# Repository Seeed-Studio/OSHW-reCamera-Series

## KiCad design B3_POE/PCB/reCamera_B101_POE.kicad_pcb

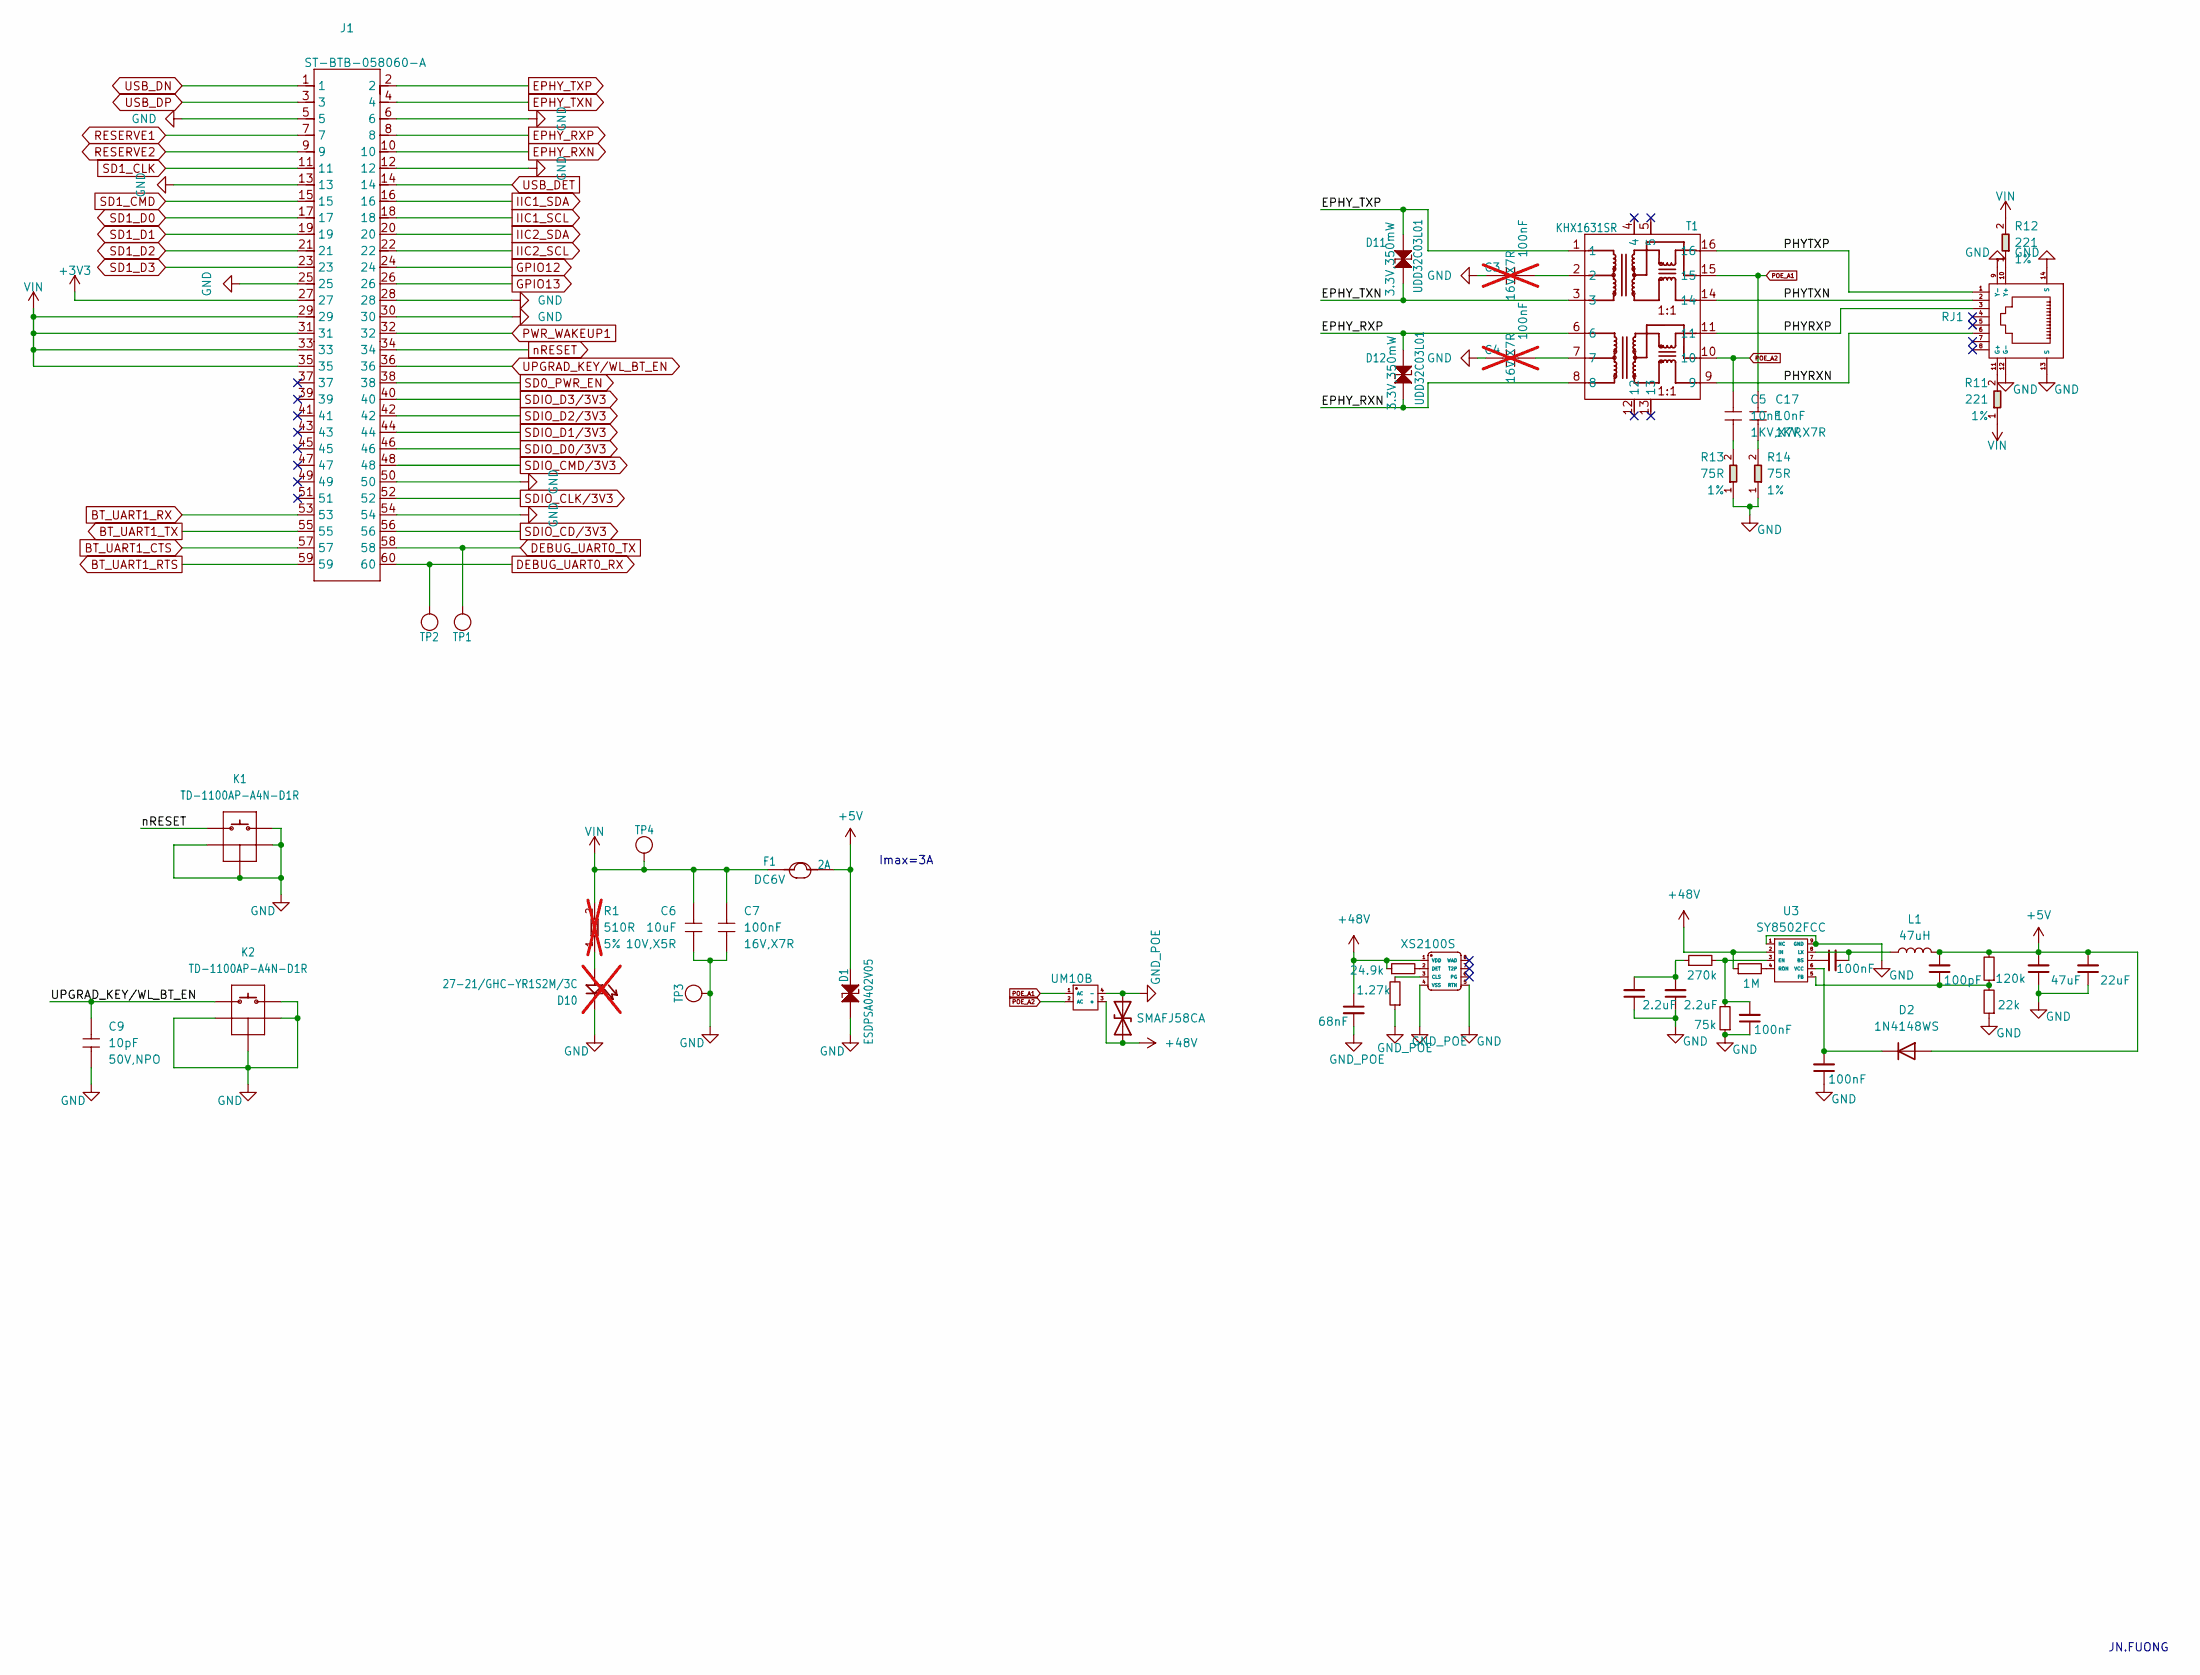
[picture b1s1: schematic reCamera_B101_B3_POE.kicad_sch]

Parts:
C1: 68nF; C_0402_1005Metric
C2, C10: 2.2uF; C_0402_1005Metric
C3, C4: 100nF; C0402; Voltage Rating 16V,X7R; MPN CC0402KRX7R7BB104; not fitted
C5, C17: 10nF; C0402; Voltage Rating 1KV,X7R; MPN CC1206KKX7RCBB102
C6: 10uF; C0402; Voltage Rating 10V,X5R; MPN CC0603KRX5R6BB106
C7: 100nF; C0402; Voltage Rating 16V,X7R; MPN CC0402KRX7R7BB104
C9: 10pF; C0402; Voltage Rating 50V,NPO; MPN CC0402JRNPO9BN100
C11, C12, C13: 100nF; C_0402_1005Metric
C14: 100pF; C_0402_1005Metric
C15: 47uF; C_0402_1005Metric
C16: 22uF; C_0402_1005Metric
D1: ESDPSA0402V05; ESD-0402; MPN ESDPSA0402V05
D2: 1N4148WS; D_SOD-323
D10: 27-21/GHC-YR1S2M/3C; LED2-0.6X1.7MM; MPN 27-21/GHC-YR1S2M/3C; not fitted
D11, D12: UDD32C03L01; SOD-323; Rating 3.3V,350mW; MPN UDD32C03L01
D13: SMAFJ58CA; SMAF_L3.5-W2.6-LS4.7-BI
F1: 2A; F1210; Rating DC6V; MPN SMD1210R200SF
J1: ST-BTB-058060-A; BTB60-Male-Female-0.5-17.7x4.4mm; MPN ST-BTB-058060-A
K1, K2: TD-1100AP-A4N-D1R; SW5-SMD-4.56X2.3X1.9MM; MPN TD-1100AP-A4N-D1R
L1: 47uH; L_7.3x7.3_H3.5
R1: 510R; R0402; Power Rating 5%; MPN RC0402JR-07510RL; not fitted
R4: 1.27k; R_0402_1005Metric
R5: 24.9k; R_0402_1005Metric
R6: 270k; R_0402_1005Metric
R7: 75k; R_0402_1005Metric
R8: 1M; R_0402_1005Metric
R9: 120k; R_0402_1005Metric
R10: 22k; R_0402_1005Metric
R11, R12: 221; C0402; Power Rating 1%; MPN RC0603FR-0775RL
R13, R14: 75R; C0402; Power Rating 1%; MPN RC0603FR-0775RL
RJ1: R-RJ45S08P-C000
T1: KHX1631SR; TRF_16p_1d27_12d7x7d15x5d1mm; MPN KHX1631SR
TP1, TP2, TP3, TP4: Test Point; TP; Part Type Test Point
U1: UM10B; UMB-4_L3.8-W3.6-P2.50-LS4.9-BL
U2: XS2100S; SOP-8_L4.9-W3.9-P1.27-LS6.0-BL
U3: SY8502FCC; SOIC-8_L4.9-W3.9-P1.27-LS6.0-BL-EP

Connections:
+3V3: J1.27
+5V: C14.2, C15.2, C16.2, D1.1, D2.2 (A), F1.2, L1.2, R9.2
+48V: C1.1, D13.1 (A1), R5.1, R8.1, U1.3 (+), U2.1 (VDD), U3.2 (IN)
/PHYRXN: RJ1.6, T1.9
/PHYRXP: RJ1.3, T1.11
/PHYTXN: RJ1.2, T1.14
/PHYTXP: RJ1.1, T1.16
BT_UART1_CTS: J1.57
BT_UART1_RTS: J1.59
BT_UART1_RX: J1.53
BT_UART1_TX: J1.55
DEBUG_UART0_RX: J1.60, TP2.1 (T)
DEBUG_UART0_TX: J1.58, TP1.1 (T)
EPHY_RXN: D12.1, J1.10, T1.8
EPHY_RXP: D12.2, J1.8, T1.6
EPHY_TXN: D11.1, J1.4, T1.3
EPHY_TXP: D11.2, J1.2, T1.1
GND: C2.1, C3.1, C4.1, C6.2, C7.2, C9.2, C10.1, C11.1, C12.1, C15.1, C16.1, D1.2, D10.2 (-), J1.5, J1.6, J1.12, J1.13, J1.25, J1.28, J1.30, J1.50, J1.54, K1.2, K1.S1, K1.S2, K1.S3, K2.2, K2.S1, K2.S2, K2.S3, R7.1, R10.1, R13.1, R14.1, RJ1.9 (Y-), RJ1.12 (G-), RJ1.13 (S), RJ1.14 (S), TP3.1 (T), U2.5 (RTN), U3.1 (NC), U3.9 (GND)
GND_POE: C1.2, D13.2 (A2), R4.1, U1.4 (-), U2.4 (VSS)
GPIO12: J1.24
GPIO13: J1.26
IIC1_SCL: J1.18
IIC1_SDA: J1.16
IIC2_SCL: J1.22
IIC2_SDA: J1.20
unnamed: C3.2, T1.2
unnamed: C4.2, T1.7
unnamed: C5.2, R13.2
unnamed: C2.2, C10.2, R6.1
unnamed: C17.2, R14.2
unnamed: C12.2, D2.1 (K), U3.6 (VCC)
unnamed: D10.1 (+), R1.1
unnamed: R11.2, RJ1.11 (G+)
unnamed: R12.1, RJ1.10 (Y+)
unnamed: R4.2, U2.3 (CLS)
unnamed: R5.2, U2.2 (DET)
unnamed: C13.1, U3.7 (BS)
unnamed: C11.2, R6.2, R7.2, U3.3 (EN)
unnamed: C14.1, R9.1, R10.2, U3.5 (FB)
unnamed: C13.2, L1.1, U3.8 (LX)
unnamed: R8.2, U3.4 (RON)
POE_A1: C17.1, T1.15, U1.1 (AC)
POE_A2: C5.1, T1.10, U1.2 (AC)
PWR_WAKEUP1: J1.32
RESERVE1: J1.7
RESERVE2: J1.9
SD0_PWR_EN: J1.38
SD1_CLK: J1.11
SD1_CMD: J1.15
SD1_D0: J1.17
SD1_D1: J1.19
SD1_D2: J1.21
SD1_D3: J1.23
SDIO_CD/3V3: J1.56
SDIO_CLK/3V3: J1.52
SDIO_CMD/3V3: J1.48
SDIO_D0/3V3: J1.46
SDIO_D1/3V3: J1.44
SDIO_D2/3V3: J1.42
SDIO_D3/3V3: J1.40
UPGRAD_KEY/WL_BT_EN: C9.1, J1.36, K2.1
USB_DET: J1.14
USB_DN: J1.1
USB_DP: J1.3
VIN: C6.1, C7.1, F1.1, J1.29, J1.31, J1.33, J1.35, R1.2, R11.1, R12.2, TP4.1 (T)
nRESET: J1.34, K1.1

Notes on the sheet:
JN.FUONG
Imax=3A

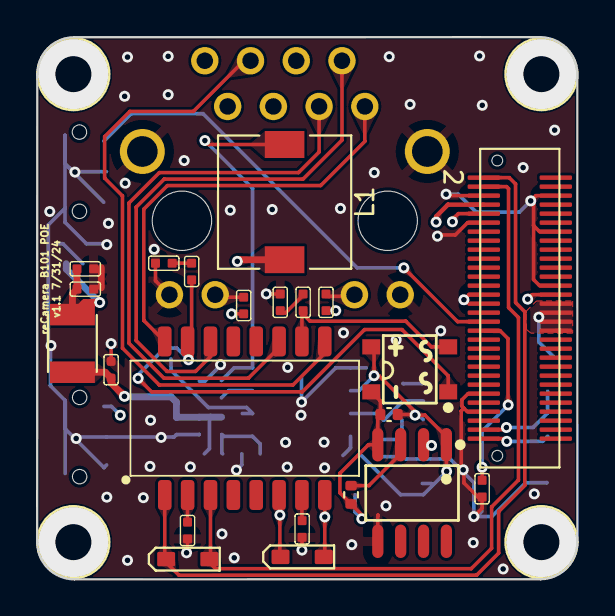
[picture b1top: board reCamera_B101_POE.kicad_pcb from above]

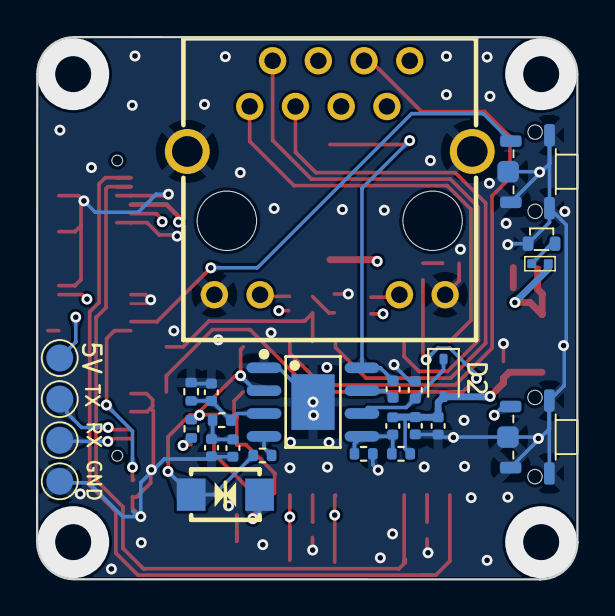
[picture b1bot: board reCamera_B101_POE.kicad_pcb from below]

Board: 4 copper layers, 30.0 x 30.1 mm, 48 parts (26 on the bottom side), 35 nets.

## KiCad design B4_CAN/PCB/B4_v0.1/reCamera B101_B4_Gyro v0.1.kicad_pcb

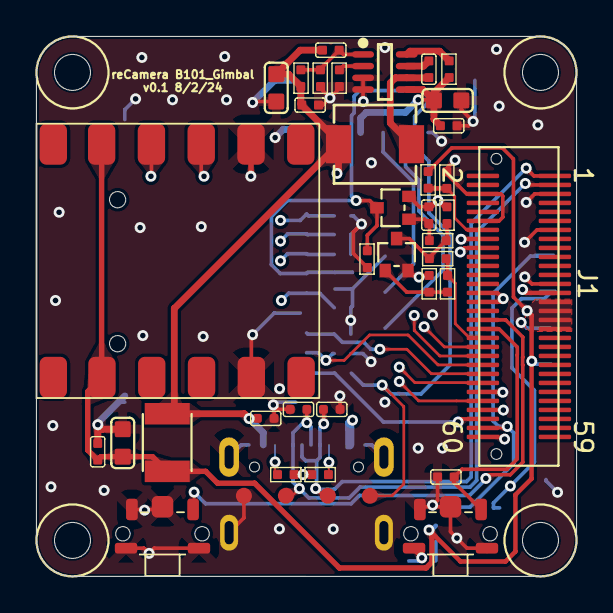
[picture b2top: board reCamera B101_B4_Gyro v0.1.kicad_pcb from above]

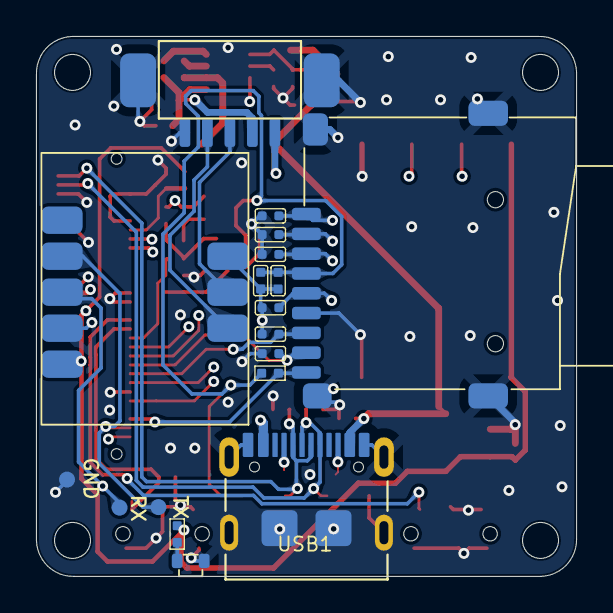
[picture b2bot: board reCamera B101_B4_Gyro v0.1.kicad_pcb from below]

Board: 4 copper layers, 30.0 x 30.0 mm, 58 parts (18 on the bottom side), 36 nets.

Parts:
C1: 1uF; C0402
C2, C3, C7, C8, C12: 100nF; C0402
C4, C11: 47uF; C0603
C5: 10nF; C0402
C6: 10uF; C0603
C9: 10pF; C0402
C10: 100pF; C0402
D1, D2, D3, D4, D5, D6, D7, D8, D9: ESDPSA0402V05; ESD-0402
D10: 27-21/GHC-YR1S2M/3C; LED2-0.6X1.7MM
F1: 2A; F1210
J1: ST-BTB-058060-A; BTB60-Male-Female-0.5-17.7x4.4mm
J2: ST-TF-003J; MICRO-SD-CARD-9P
J3: 1.25-5A-WT; JST5_2P_1d25_7_9x4_3x3_4mm
K1, K2: TD-1100AP-A4N-D1R; SW5-SMD-4.56X2.3X1.9MM
L1: 6.8uH
Q1: S9013W; SOT-323
Q2: CJ2101; SOT-323
R1: 510R; R0402
R2, R24: 1K; R0402
R3, R9, R21, R23: 100K; R0402
R4: 10K; R0402
R5: 20K; R0402
R6: 200k; R0402
R7, R12: 5.1K; R0402
R8: 10k; R0402
R10: 13.7k; R0402
R20: 47K; R0402
R22: 33K; R0402
TP1, TP2, TP3, TP4, TP5, TP6, TP7: Test Point; TP-D35MIL
U1: WT9011G4K
U2: TTL-CAN
U4: SY8303AIC
USB1: USB2.0 Type C; USB2.0-TYPE-C

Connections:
+3V3: C8.1, J1.27, Q2.2 (S), R22.2
+5V: C10.1, C11.1, C12.1, D1.1, F1.2, J3.1, L1.2, R9.2, USB1.A4_B9 (A4/B9/VBUS), USB1.B4_A9 (B4/A9/VBUS)
+12V: C3.1, C4.1, J3.2, R8.1, U4.5 (IN)
CANH: J3.4, U2.8 (CANH)
CANL: J3.3, U2.7 (CANL)
DEBUG_UART0_RX: J1.60, TP2.1 (T), U2.3 (R)
DEBUG_UART0_TX: J1.58, TP1.1 (T), U2.2 (T)
GND: C1.2, C2.2, C3.2, C4.2, C6.2, C7.2, C9.2, C11.2, C12.2, D1.2, D2.2, D3.2, D4.2, D5.2, D6.2, D7.2, D8.2, D9.2, D10.2 (-), J1.5, J1.6, J1.12, J1.13, J1.25, J1.28, J1.30, J1.50, J1.54, J2.S1 (SHD1), J2.S2 (SHD2), J2.S3 (SHD3), J2.S4 (SHD4), J2.T6 (VSS), J3.5, J3.6, J3.7, K1.2, K1.S1, K1.S2, K1.S3, K2.2, K2.S1, K2.S2, K2.S3, Q1.2 (E), R3.1, R4.1, R6.1, R7.1, R10.1, R12.2, R21.1, TP3.1 (T), TP6.1 (T), U1.5 (GND), U1.11 (GND), U2.4 (GND), U2.6 (GND), U4.3 (GND), U4.4 (GND), USB1.A1_B12 (A1/B12/GND), USB1.B1_A12 (B1/A12/GND), USB1.S1, USB1.S2, USB1.S3, USB1.S4, USB1.S5, USB1.S6
IIC1_SCL: J1.18, U1.9 (SCL)
IIC1_SDA: J1.16, U1.10 (SDA)
unnamed: D10.1 (+), R1.1
unnamed: Q1.1 (B), R2.2, R3.2
unnamed: Q1.3 (C), R20.1, R22.1, R24.1
unnamed: C8.2, Q2.1 (G), R20.2
unnamed: C5.2, U4.7 (BS)
unnamed: R8.2, U4.8 (EN)
unnamed: C10.2, R9.1, R10.2, U4.1 (FB)
unnamed: R6.2, U4.2 (FS)
unnamed: C5.1, L1.1, U4.6 (LX)
unnamed: R12.1, USB1.A5 (A5/CC1)
unnamed: R7.2, USB1.B5 (B5/CC2)
SD0_PWR_EN: J1.38, R2.1, R24.2
SDIO_CD/3V3: J1.56, J2.G1 (SWITCH), R23.1
SDIO_CLK/3V3: D6.1, J1.52, J2.T5 (CLOCK)
SDIO_CMD/3V3: D7.1, J1.48, J2.T3 (CMD)
SDIO_D0/3V3: D5.1, J1.46, J2.T7 (DAT0)
SDIO_D1/3V3: D4.1, J1.44, J2.T8 (DAT1)
SDIO_D2/3V3: D9.1, J1.42, J2.T1 (DAT2)
SDIO_D3/3V3: D8.1, J1.40, J2.T2 (CD/DAT3)
SD_PWR_3V3: C1.1, C2.1, J2.T4 (VDD), Q2.3 (D), R21.2, R23.2, TP7.1 (T)
UPGRAD_KEY/WL_BT_EN: C9.1, J1.36, K2.1
USB_DET: J1.14, R4.2, R5.1
USB_DN: D2.1, J1.1, TP4.1 (T), USB1.A7 (A7/DN1), USB1.B7 (B7/DN2)
USB_DP: D3.1, J1.3, TP5.1 (T), USB1.A6 (A6/DP1), USB1.B6 (B6/DP2)
VIN: C6.1, C7.1, F1.1, J1.29, J1.31, J1.33, J1.35, R1.2, R5.2, U1.2 (VCC), U1.8 (VCC), U2.5 (VCC)
nRESET: J1.34, K1.1

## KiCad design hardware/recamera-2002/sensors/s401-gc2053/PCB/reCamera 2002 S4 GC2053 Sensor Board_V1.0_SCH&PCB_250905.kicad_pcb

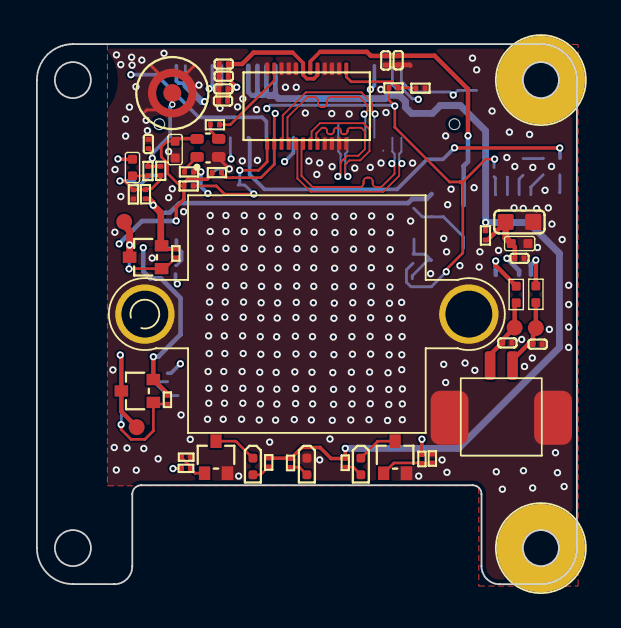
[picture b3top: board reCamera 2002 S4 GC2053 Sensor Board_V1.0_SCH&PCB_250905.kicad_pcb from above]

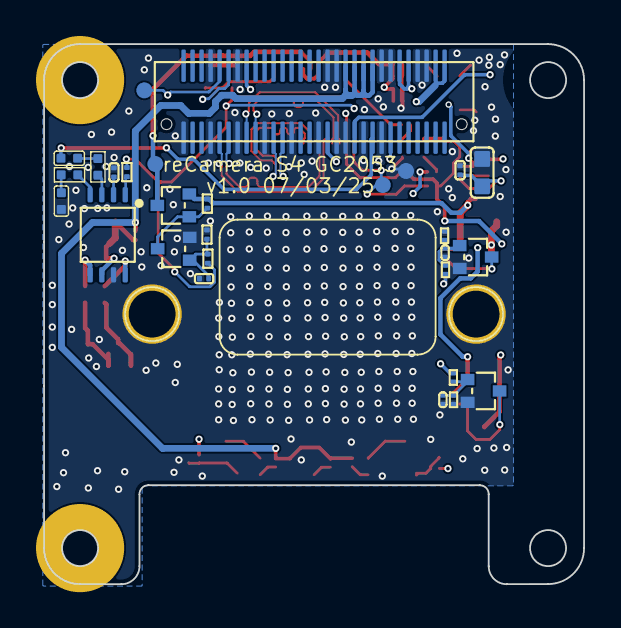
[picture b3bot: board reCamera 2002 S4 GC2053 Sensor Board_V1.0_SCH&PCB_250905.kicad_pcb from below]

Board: 4 copper layers, 30.0 x 30.0 mm, 83 parts (30 on the bottom side), 51 nets.

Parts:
C1: 100pF; C0201
C2: 22uF; C0603
C3, C7, C8, C9, C21, C23, C26, C27, C28: 100nF; C0201
C4, C18, C19: 2.2uF; C0402
C10, C22: 1uF; C0402
C15, C16, C17: 1uF; C0201
C20: 10uF; C0603
C24, C25: 1nF; C0201
D5: Green; LED-0402
D6: Red; LED-0402
D7: Blue; LED-0402
J1: ST-BTB-058060-B; BTB60-Male-Female-0.5-17.7x4.4mm
J2: DF30FC-24DS-0.4V; BTB2x12P_0d4_7_02x3_76x0_9mm
J3: 1.25-2A-WT; GH2-1.25-7.4X5.3X3.5MM
M1, M2: PTH_5X2MM
M3, M4: SMTSOM1.610BTR; M1.6-D3.18MM
MIC1: HMD-4013B423-CR1; MIC-5P-SMD-4X4MM
Q2, Q4, Q5, Q7, Q9: LBSS138WT1G; SOT-323
Q3, Q6, Q8: CJ2101; SOT-323
R1: 2.2K; R0201
R2: 2.2R; R0201
R3: 1.2K; R0201
R4: 680R; R0201
R6, R11: 4.7K; R0201
R7, R8, R15: 10K; R0201
R9, R25, R26, R27, R29, R31, R33, R34, R35: 1K; R0201
R12, R13: 30K; R0402
R14, R18: 0R; R0201
R16, R17: 0R; R0402
R22, R23, R24, R30, R36, R37: 100K; R0201
R28, R32: 47K; R0201
TP5, TP6, TP7, TP8, TP9, TP10, TP11, TP12: Test Point; TP-D35MIL
U3: NS4150B; MSOP8-0.65-3X3X1MM
X1: 9C24000004; X4-SMD-2.0X1.6MM

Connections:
1V8: J1.49, J1.51, Q6.2 (S), R24.2
3V3: J1.57, J1.59, Q3.2 (S), Q8.2 (S), R4.2, R22.2, R36.2
/24MHz: J2.4, R18.2
AUD_AOUTR: C18.1, J1.44
AUD_MIC: C4.1, J1.40
AVDD: C7.1, C9.1, C15.1, C17.1, J2.12, J2.16, Q8.3 (D), TP12.1 (T)
CAM_1V8: C10.1, Q6.3 (D), R6.2, R11.2, TP11.1 (T), X1.4 (VDD)
CAM_EN: J1.48, R8.1, R9.2, R15.2, R25.1, R27.1, R35.1
CAM_I2C2_SCL: J1.9, J2.3, R11.1, TP10.1 (T)
CAM_I2C2_SDA: J1.11, J2.1, R6.1, TP9.1 (T)
CAM_RX0_0N: J1.16, J2.5
CAM_RX0_0P: J1.18, J2.7
CAM_RX0_1N: J1.22, J2.13
CAM_RX0_1P: J1.24, J2.15
CAM_RX0_CLKN: J1.10, J2.9
CAM_RX0_CLKP: J1.12, J2.11
GND: C1.2, C2.2, C3.2, C7.2, C8.2, C9.2, C10.2, C15.2, C16.2, C17.2, C19.1, C20.2, C21.2, C22.2, C23.2, C24.2, C25.2, C26.2, C27.2, C28.2, D5.2 (-), J1.2, J1.7, J1.8, J1.13, J1.14, J1.20, J1.26, J1.32, J1.33, J1.35, J1.36, J1.38, J1.42, J1.45, J1.46, J1.47, J1.53, J1.55, J2.2, J2.6, J2.8, J2.10, J2.17, J2.18, J2.19, J2.20, J2.21, J2.22, J2.23, J3.3, J3.4, M3.1, M4.1, MIC1.2 (-), MIC1.3 (-), MIC1.4 (-), Q2.2 (S), Q4.2 (S), Q5.2 (S), Q7.2 (S), Q9.2 (S), R3.1, R7.1, R23.1, R28.1, R30.1, R32.1, R37.1, TP7.1 (T), U3.7 (GND), X1.2 (GND)
GPIO15/IR_CUT: J1.34, R26.1
IOVDD: C8.1, C16.1, J2.14, Q3.3 (D), TP8.1 (T)
IR_PWM: J1.15, R31.1
unnamed: C2.1, C3.1, R1.1, R3.2, R4.1
unnamed: C4.2, R2.2
unnamed: C18.2, R12.1
unnamed: C19.2, R13.1
unnamed: D5.1 (+), R34.1
unnamed: D6.1 (+), R29.1
unnamed: D6.2 (-), Q4.3 (D)
unnamed: D7.1 (+), R33.1
unnamed: D7.2 (-), Q5.3 (D)
unnamed: J2.24, R7.2, R8.2
unnamed: C1.1, MIC1.1 (+), R1.2, R2.1
unnamed: Q2.3 (D), Q3.1 (G), R22.1
unnamed: C26.1, Q2.1 (G), R23.2, R25.2
unnamed: Q4.1 (G), R26.2, R28.2
unnamed: Q5.1 (G), R31.2, R32.2
unnamed: Q6.1 (G), Q7.3 (D), R24.1
unnamed: C27.1, Q7.1 (G), R27.2, R30.2
unnamed: Q8.1 (G), Q9.3 (D), R36.1
unnamed: C28.1, Q9.1 (G), R35.2, R37.2
unnamed: C24.1, J3.2, R17.2, TP5.1 (T)
unnamed: C25.1, J3.1, R16.2, TP6.1 (T)
unnamed: C23.1, U3.2 (Bypass)
unnamed: R15.1, U3.1 (CTRL)
unnamed: R13.2, U3.4 (INN)
unnamed: R12.2, U3.3 (INP)
unnamed: C20.1, C21.1, C22.1, R14.2, U3.6 (VCC)
unnamed: R16.1, U3.5 (VoN)
unnamed: R17.1, U3.8 (VoP)
unnamed: R18.1, X1.3 (CLK)
unnamed: R9.1, X1.1 (ENABLE)
VIN: J1.37, J1.39, J1.41, J1.43, R14.1, R29.2, R33.2, R34.2

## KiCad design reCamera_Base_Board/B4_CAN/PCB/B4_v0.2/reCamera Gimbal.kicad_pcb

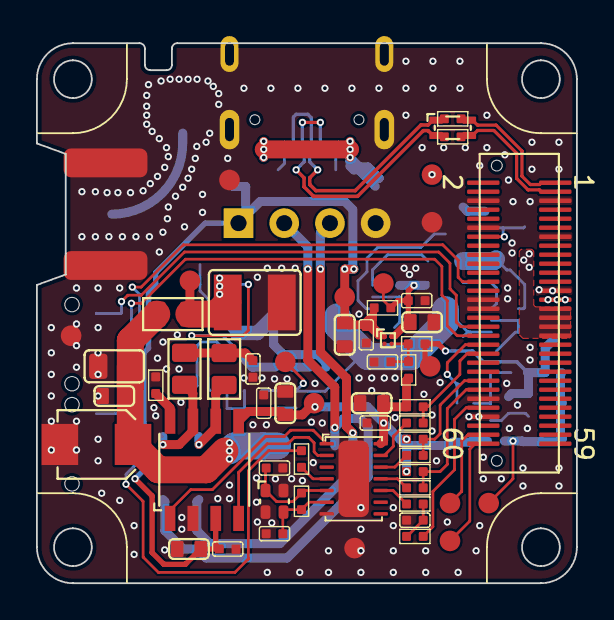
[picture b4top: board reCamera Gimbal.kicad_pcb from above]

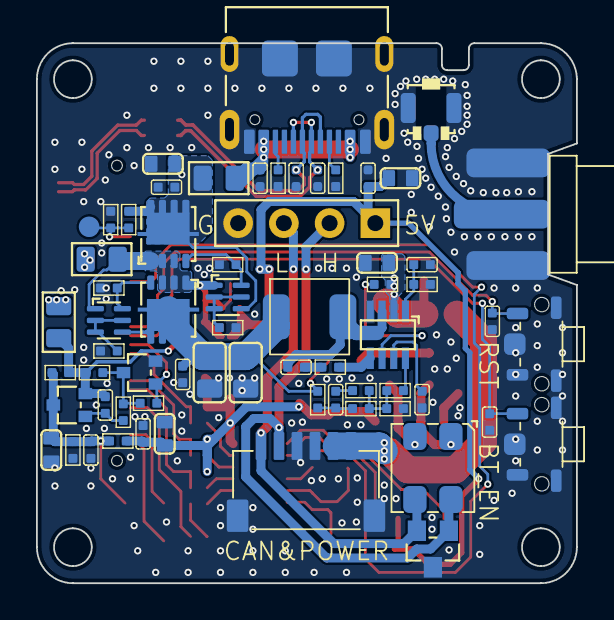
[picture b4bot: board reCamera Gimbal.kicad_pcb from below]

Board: 2 copper layers, 30.0 x 30.0 mm, 123 parts (65 on the bottom side), 64 nets.

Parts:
ANT1: U.FL-R-SMT-1; U-FL3P-SMD-2.6X2.6X1.0MM
ANT2: ANT Connect; ANTENNA-5P-13.5X6.5X6.5MM
C1: 22uF; C1210
C2, C17, C32: 100nF; C0603
C3, C5, C8, C12, C15, C16, C18, C24, C26, C28, C30, C34, C36: 100nF; C0402
C4: 1nF; C0402
C6, C7: 22uF; C0805
C9, C10, C11: 33pF; C0402
C13, C14, C19, C23, C25, C27, C29, C35: 4.7uF; C0603
C20: 10pF; C0402
C21, C22: 15pF; C0402
C31: 4.7nF; C0402
C33: 1uF; C0805
D1, D2: ESDPSA0402V05; ESD-0402
D3, D6: TPD1E10B06DPYR; ESD-0402
D4: SMBJ24CA; DO-214AA_SMB
D5: SM05-7; SOT-23
FB1: 120R; L0402
FB2, FB3, FB4, FB5: 0R; L0805
J1: ST-BTB-058060-A; BTB60-Male-Female-0.5-17.7x4.4mm
J2: SM06B-SRSS-TB(LF)(SN); SMD-SH1.0-6P-90D
J3: FF-1025; H4-2.54-65_35MIL
K1, K2: TD-1100AP-A4N-D1R; SW5-SMD-4.56X2.3X1.9MM
L1: 5.6uH-20%; INT2-SMD-4.2X4.4X1.8MM
L2: 90R; INT4-0.85-2X1.25X1.2MM
L3: PCAQ4520MB-142; INT4-1.5-4.75X4.5X2MM
Q1: LMUN5233T1G; SOT-323
Q2: CJ2101; SOT-323
Q3, Q4: RQ3E120ATTB; DFN8P-0.65-3X3X0.8MM
R1, R2: 5.1K; R0402
R3, R4: 5.1R; R0402
R5: 75K; R0402
R6, R19, R35, R36, R37, R38: 100K; R0402
R7, R15: 20K; R0402
R8, R12: 20R; R0402
R9: 40.2K; R0402
R10: 7.5k; R0402
R11, R13, R20, R21, R22, R23, R24, R25, R26, R31, R32, R39: 0R; R0402
R14: 11k; R0402
R16: 33K; R0402
R17: 47K; R0402
R18: 1K; R0402
R27, R28, R29: 4.7K; R0402
R30: 1M; R0402
R33, R34: 62R; R0805
TP1, TP2, TP3, TP4, TP5, TP6, TP7, TP8, TP9, TP10, TP11, TP12, TP13, TP14, TP15: Test Point; TP-D45MIL
U1: MP2315GJ; TSOT23-8
U2: MCP2518FDT-E/QBB; VDFN14-0.65-4.5X3X0.85MM
U3: MCP2558FD-H/SN; SOIC8-1.27-5X4MM
U4: TPS22916CYFPR; WLCSP4-0.4-0.77X0.77X0.33MM
U5, U6: BC856S; SOT-363
USB1: USB-31C-F-16P-L7.35; USB2.0-TYPE-C
X1: 40MHz; X4-SMD-2.0X1.6MM

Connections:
+3V3: C12.1, FB4.1, Q2.2 (S), R16.2, R20.1, R31.1, TP15.1 (T)
/03 Power/5V_DC_EN: R6.2, U1.6 (EN/SYNC)
/03 Power/DCDC_VCC: C3.1, U1.7 (VCC)
/03 Power/USBC_D_N: D1.2, L2.1, R3.1, USB1.A7 (A7/DN1), USB1.B7 (B7/DN2)
/03 Power/USBC_D_P: D2.2, L2.4, R4.1, USB1.A6 (A6/DP1), USB1.B6 (B6/DP2)
/04 CAN/CANH: L3.1, R33.2, U3.7 (CAN_H)
/04 CAN/CANL: L3.4, R34.1, U3.6 (CAN_L)
/04 CAN/CAN_H: D5.1, J2.5, J3.2, L3.2
/04 CAN/CAN_L: D5.2, J2.6, J3.3, L3.3
/04 CAN/RF_LINE: ANT1.1 (D), ANT2.1 (ANT)
CAN_3V3: C18.1, C19.1, C23.1, C24.1, C35.1, C36.1, FB1.2, R27.2, R28.2, R29.2, R32.1, TP12.1 (T), U2.14 (VDD), U3.5 (VIO)
CAN_5V: C17.1, C27.1, C28.1, C29.1, C30.1, D6.2, J3.1, R39.2, TP14.1 (T), U3.3 (VDD), U4.A1 (VOUT)
DCDC_5V: C6.1, C7.1, C8.1, L1.2, Q3.5 (D1), Q3.6 (D2), Q3.7 (D3), Q3.8 (D4), Q3.9 (D5), R8.2, TP7.1 (T), U5.4
DC_IN: C1.1, C2.1, FB5.1, R6.1, TP5.1 (T), U1.2 (IN)
DEBUG_UART0_RX: J1.60, TP2.1 (T)
DEBUG_UART0_TX: J1.58, TP1.1 (T)
GND: ANT1.2 (GND1), ANT1.3 (GND2), ANT2.2 (5), ANT2.3 (4), ANT2.4 (3), ANT2.5 (2), C1.2, C2.2, C3.2, C4.2, C6.2, C7.2, C8.2, C10.2, C11.2, C13.2, C14.2, C15.2, C16.2, C17.2, C18.2, C19.2, C20.2, C21.2, C22.2, C23.2, C24.2, C25.2, C26.2, C27.2, C28.2, C29.2, C30.2, C31.2, C32.2, C33.2, C34.2, C35.2, C36.2, D1.1, D2.1, D3.1, D4.1 (+), D5.3, D6.1, J1.5, J1.6, J1.12, J1.13, J1.25, J1.28, J1.30, J1.50, J1.54, J2.3, J2.4, J2.7, J2.8, J3.4, K1.2, K1.S1, K1.S2, K1.S3, K2.2, K2.S1, K2.S2, K2.S3, Q1.2 (E), R1.1, R2.2, R5.1, R10.1, R13.1, R14.1, R19.1, R35.1, R36.1, R37.1, R38.1, TP4.1 (T), TP6.1 (T), TP8.1 (T), TP13.1 (T), U1.4 (GND), U2.7 (VSS), U2.15 (EP), U3.2 (VSS), U4.B1 (GND), USB1.A1_B12 (A1/B12/GND), USB1.B1_A12 (B1/A12/GND), USB1.S1, USB1.S2, USB1.S3, USB1.S4, USB1.S5, USB1.S6, X1.2, X1.4
GPIO12: J1.24, R26.1
unnamed: C5.1, R12.2
unnamed: C9.1, R11.2
unnamed: C9.2, R8.1, R9.2
unnamed: C31.1, R33.1, R34.2
unnamed: C32.1, C33.1, D4.2 (-), FB5.2, J2.1, J2.2
unnamed: FB3.2, J1.29, J1.31, J1.33, J1.35
unnamed: FB4.2, J1.27
unnamed: J1.52, R21.1
unnamed: Q1.3 (C), R16.1, R17.1, R18.1
unnamed: C12.2, Q2.1 (G), R17.2
unnamed: Q3.4 (G), R36.2, U5.6
unnamed: Q4.4 (G), R38.2, U6.6
unnamed: R7.2, R9.1, R10.2, R11.1
unnamed: R35.2, U5.2, U5.3, U5.5
unnamed: R37.2, U6.2, U6.3, U6.5
unnamed: C4.1, R5.2, U1.1 (AAM)
unnamed: R12.1, U1.5 (BST)
unnamed: R7.1, U1.8 (FB)
unnamed: C5.2, L1.1, U1.3 (SW)
unnamed: C22.1, R30.2, U2.6 (OSC1), X1.3
unnamed: C21.1, R30.1, U2.5 (OSC2), X1.1
unnamed: U2.2 (RXCAN), U3.4 (RXD)
unnamed: R22.2, U2.10 (SCK)
unnamed: R24.2, U2.11 (SDI)
unnamed: R25.2, U2.12 (SDO)
unnamed: U2.1 (TXCAN), U3.1 (TXD)
unnamed: R23.2, U2.13 (nCS)
unnamed: R26.2, U2.4 (~INT)
unnamed: R13.2, U3.8 (S)
unnamed: C34.1, R31.2, R32.2, U4.B2 (EN)
unnamed: D3.2, FB2.1, USB1.A4_B9 (A4/B9/VBUS), USB1.B4_A9 (B4/A9/VBUS)
unnamed: R1.2, USB1.A5 (A5/CC1)
unnamed: R2.1, USB1.B5 (B5/CC2)
SD0_PWR_3V3: C13.1, C16.1, FB1.1, Q2.3 (D), R19.2, R20.2, TP11.1 (T)
SD0_PWR_EN: J1.38, Q1.1 (B), R18.2
SDIO_CLK/3V3: C20.1, R21.2, R22.1
SDIO_CMD/3V3: J1.48, R24.1, R27.1
SDIO_D0/3V3: J1.46, R25.1, R28.1
SDIO_D3/3V3: J1.40, R23.1, R29.1
UPGRAD_KEY/WL_BT_EN: C11.1, J1.36, K2.1
USB_5V: C14.1, C15.1, FB2.2, Q4.5 (D1), Q4.6 (D2), Q4.7 (D3), Q4.8 (D4), Q4.9 (D5), R15.2, TP3.1 (T), U6.4
USB_DET: J1.14, R14.2, R15.1, TP10.1 (T)
USB_D_N: J1.1, L2.2, R3.2
USB_D_P: J1.3, L2.3, R4.2
VIN: C25.1, C26.1, FB3.1, Q3.1 (S1), Q3.2 (S2), Q3.3 (S3), Q4.1 (S1), Q4.2 (S2), Q4.3 (S3), R39.1, TP9.1 (T), U4.A2 (VIN), U5.1, U6.1
nRESET: C10.1, J1.34, K1.1
